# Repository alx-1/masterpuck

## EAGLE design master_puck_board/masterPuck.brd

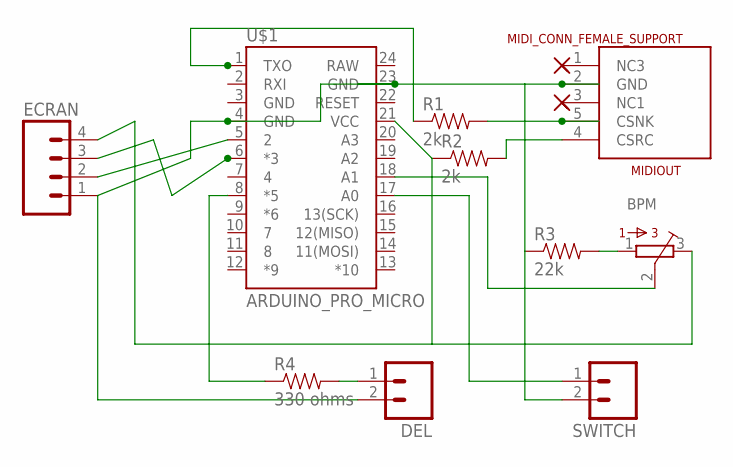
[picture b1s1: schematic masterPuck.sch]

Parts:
BPM: 3386-P; 3386P
DEL: M02LOCK; 1X02_LOCK
ECRAN: M04PTH; 1X04
MIDIOUT: MIDI_CONN_FEMALE_SUPPORT; DIN_5_FEMALE_SUPPORT
R1, R2: 2k; 1206
R3: 22k; 1206
R4: 330 ohms; 1206
SWITCH: M02LOCK; 1X02_LOCK
U$1: ARDUINO_PRO_MICRO

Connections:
GND: DEL.2, ECRAN.1, MIDIOUT.2 (GND), R3.1, SWITCH.2, U$1.4 (GND), U$1.23 (GND)
unnamed: MIDIOUT.5 (CSNK), R1.2
unnamed: MIDIOUT.4 (CSRC), R2.2
unnamed: R1.1, U$1.1 (TXO)
unnamed: ECRAN.2, U$1.5 (2)
unnamed: ECRAN.3, U$1.6 (*3)
unnamed: BPM.1, R3.2
unnamed: BPM.2, U$1.18 (A1)
unnamed: DEL.1, R4.2
unnamed: R4.1, U$1.8 (*5)
unnamed: SWITCH.1, U$1.17 (A0)
VCC: BPM.3, ECRAN.4, R2.1, U$1.21 (VCC)

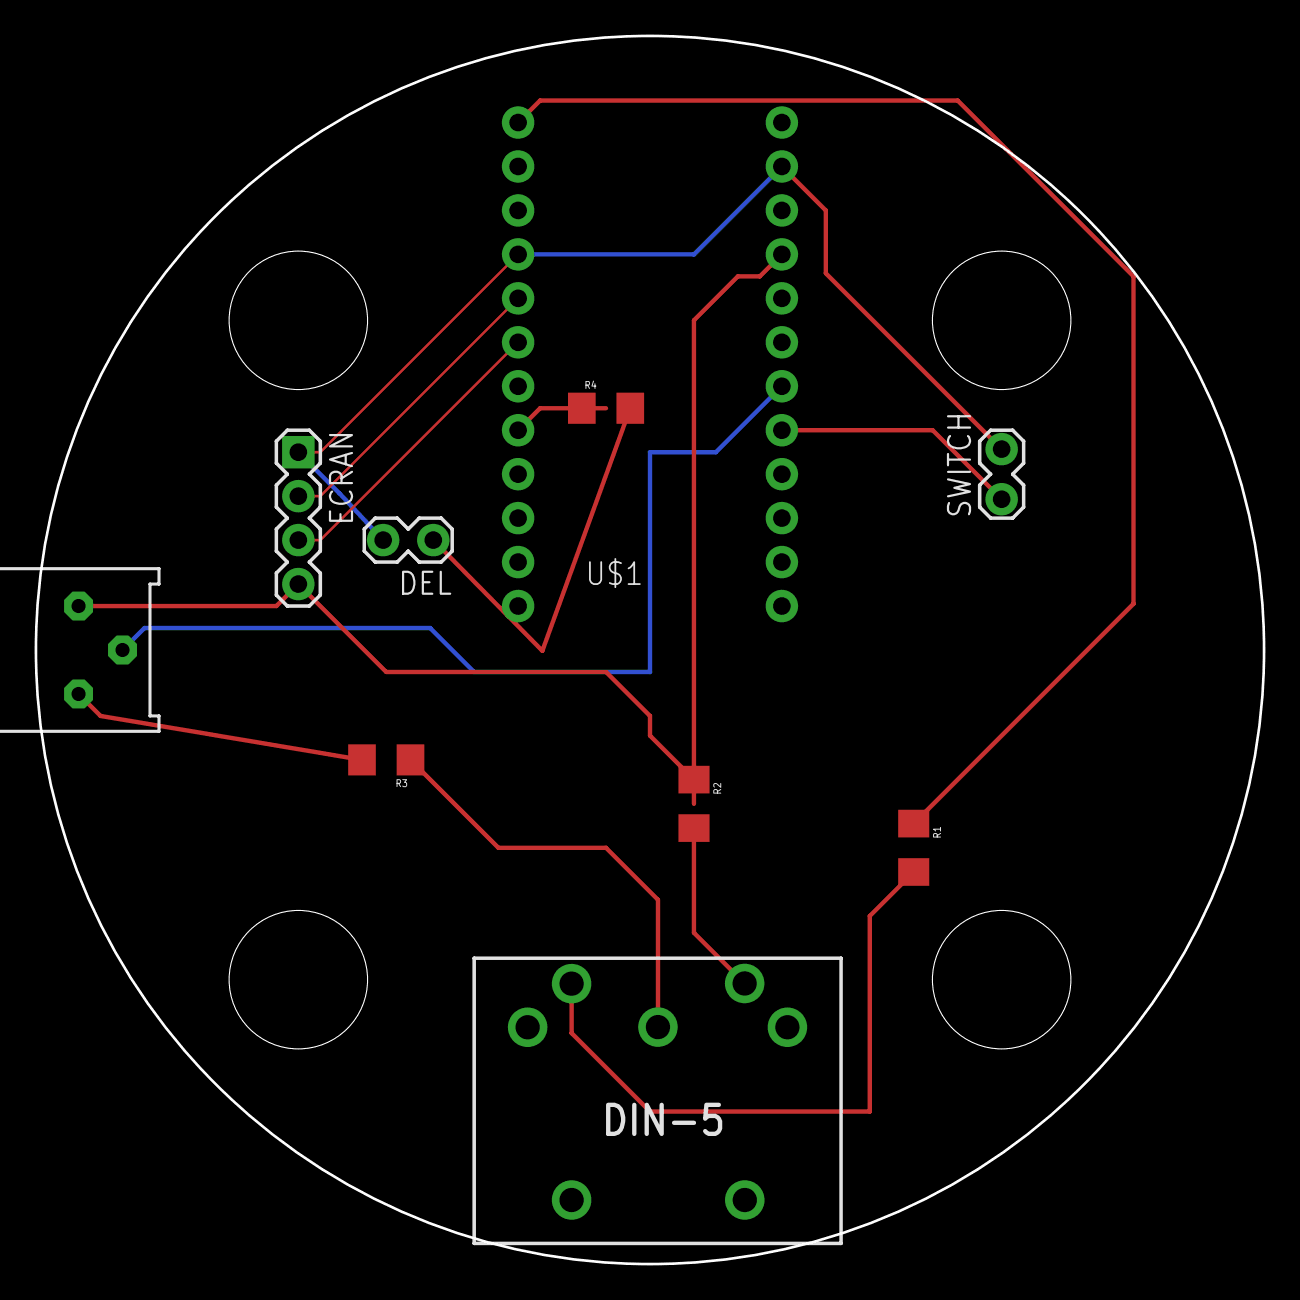
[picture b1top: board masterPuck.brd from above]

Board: 2 copper layers, 71.0 x 71.0 mm, 10 parts (0 on the bottom side), 12 nets.

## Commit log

2019-02-21 masterpuck
    A midi master clock project based on
    https://github.com/DieterVDW/arduino-midi-clock/blob/master/MIDI-Clock.i
    no
2019-02-21 board and 3D print files
    Results may vary
2019-03-20 overflow fix
2021-01-11 now with Ableton Link
    Start/stop
    SetTempo
    Smart config

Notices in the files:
parts and their libraries:
SparkFun-Boards: Licensing: Creative Commons ShareAlike 4.0 International - https://creativecommons.org/licenses/by-sa/4.0
